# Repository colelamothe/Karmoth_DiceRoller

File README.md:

# Karmoth_DiceRoller
Compact battery powered polyhedral dice set

Currently available for purchase via: https://houseoftobes-shop.fourthwall.com/en-cad/products/karmoth-roller

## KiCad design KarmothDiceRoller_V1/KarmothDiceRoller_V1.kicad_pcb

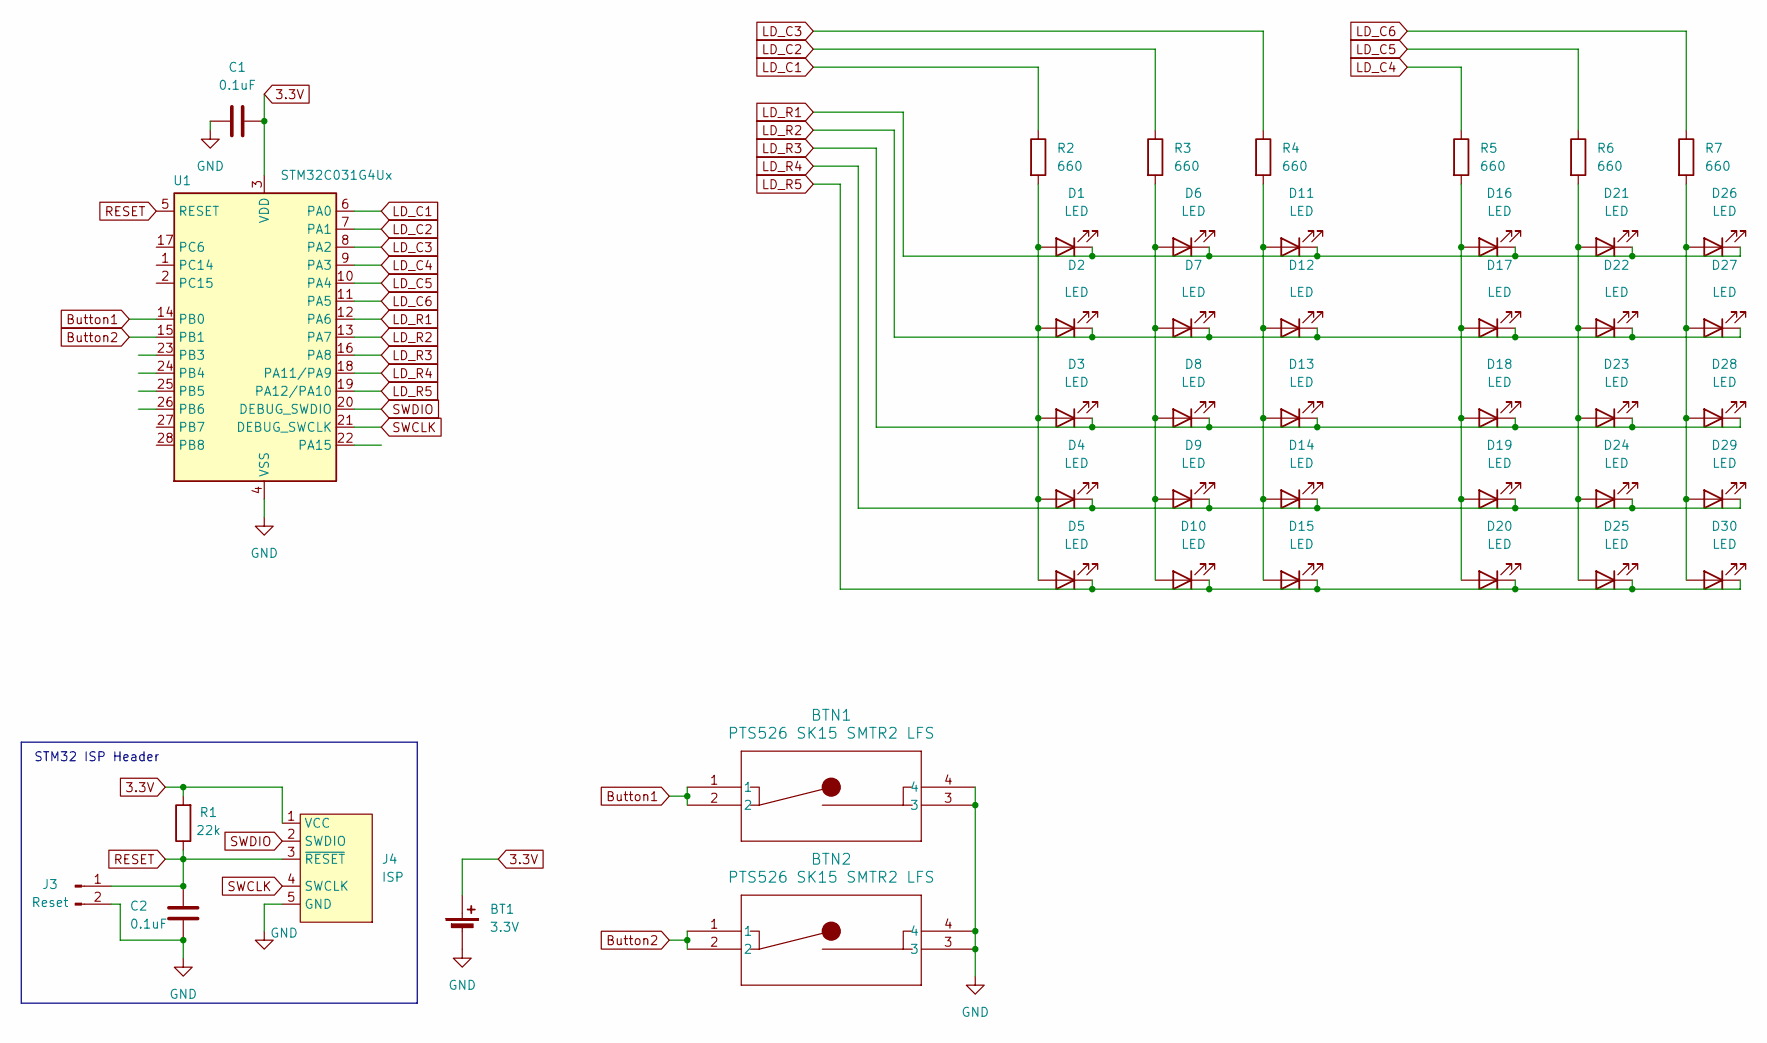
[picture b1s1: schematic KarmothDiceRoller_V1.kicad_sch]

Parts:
BT1: 3.3V; BatteryHolder_Keystone_3002_1x2032
BTN1, BTN2: PTS526 SK15 SMTR2 LFS; SMT_FS
C1, C2: 0.1uF; C_0805_2012Metric
D1, D2, D3, D4, D5, D6, D7, D8, D9, D10, D11, D12, D13, D14, D15, D16, D17, D18, D19, D20, D21, D22, D23, D24, D25, D26, D27, D28, D29, D30: LED; LED_0603_1608Metric
J3: Reset; PinHeader_1x02_P1.27mm_Vertical_SMD_Pin1Right
J4: ISP; PinHeader_1x05_P1.00mm_Vertical_SMD_Pin1Left
R1: 22k; R_0603_1608Metric
R2, R3, R4, R5, R6, R7: 660; R_0603_1608Metric
U1: STM32C031G4Ux; QFN-28_4x4mm_P0.5mm

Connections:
3.3V: BT1.1 (+), C1.1, J4.1 (VCC), R1.2, U1.3 (VDD)
Button1: BTN1.1, BTN1.2, U1.14 (PB0)
Button2: BTN2.1, BTN2.2, U1.15 (PB1)
GND: BT1.2 (-), BTN1.3, BTN1.4, BTN2.3, BTN2.4, C1.2, C2.2, J3.2, J4.5 (GND), U1.4 (VSS)
LD_C1: R2.1, U1.6 (PA0)
LD_C2: R3.1, U1.7 (PA1)
LD_C3: R4.1, U1.8 (PA2)
LD_C4: R5.1, U1.9 (PA3)
LD_C5: R6.1, U1.10 (PA4)
LD_C6: R7.1, U1.11 (PA5)
LD_R1: D1.1 (K), D6.1 (K), D11.1 (K), D16.1 (K), D21.1 (K), D26.1 (K), U1.12 (PA6)
LD_R2: D2.1 (K), D7.1 (K), D12.1 (K), D17.1 (K), D22.1 (K), D27.1 (K), U1.13 (PA7)
LD_R3: D3.1 (K), D8.1 (K), D13.1 (K), D18.1 (K), D23.1 (K), D28.1 (K), U1.16 (PA8)
LD_R4: D4.1 (K), D9.1 (K), D14.1 (K), D19.1 (K), D24.1 (K), D29.1 (K), U1.18 (PA11/PA9)
LD_R5: D5.1 (K), D10.1 (K), D15.1 (K), D20.1 (K), D25.1 (K), D30.1 (K), U1.19 (PA12/PA10)
unnamed: D1.2 (A), D2.2 (A), D3.2 (A), D4.2 (A), D5.2 (A), R2.2
unnamed: D6.2 (A), D7.2 (A), D8.2 (A), D9.2 (A), D10.2 (A), R3.2
unnamed: D11.2 (A), D12.2 (A), D13.2 (A), D14.2 (A), D15.2 (A), R4.2
unnamed: D16.2 (A), D17.2 (A), D18.2 (A), D19.2 (A), D20.2 (A), R5.2
unnamed: D21.2 (A), D22.2 (A), D23.2 (A), D24.2 (A), D25.2 (A), R6.2
unnamed: D26.2 (A), D27.2 (A), D28.2 (A), D29.2 (A), D30.2 (A), R7.2
RESET: C2.1, J3.1, J4.3 (~RESET), R1.1, U1.5 (RESET)
SWCLK: J4.4 (SWCLK), U1.21 (DEBUG_SWCLK)
SWDIO: J4.2 (SWDIO), U1.20 (DEBUG_SWDIO)

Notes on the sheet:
STM32 ISP Header

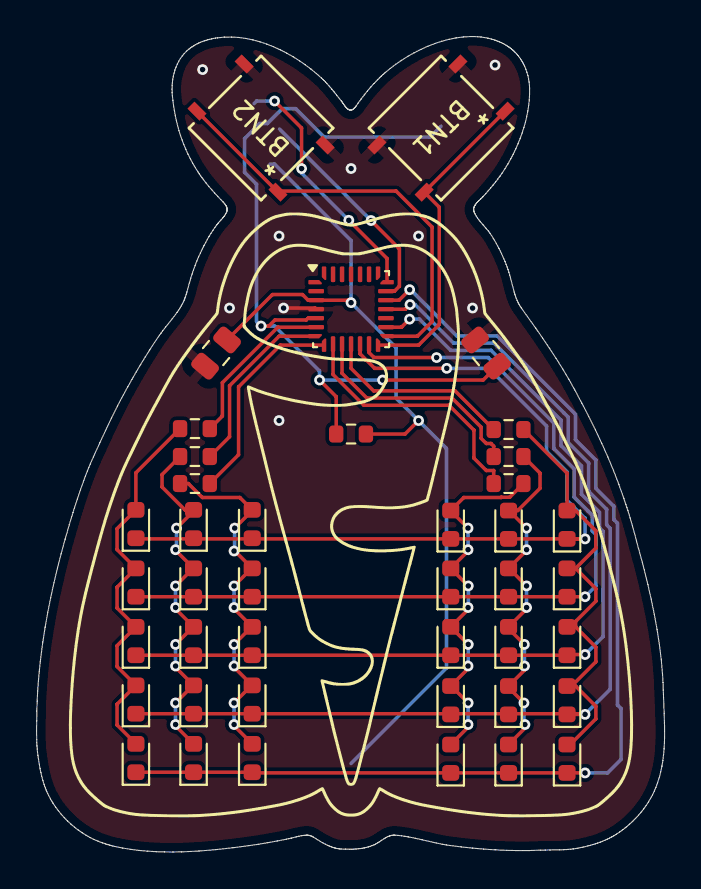
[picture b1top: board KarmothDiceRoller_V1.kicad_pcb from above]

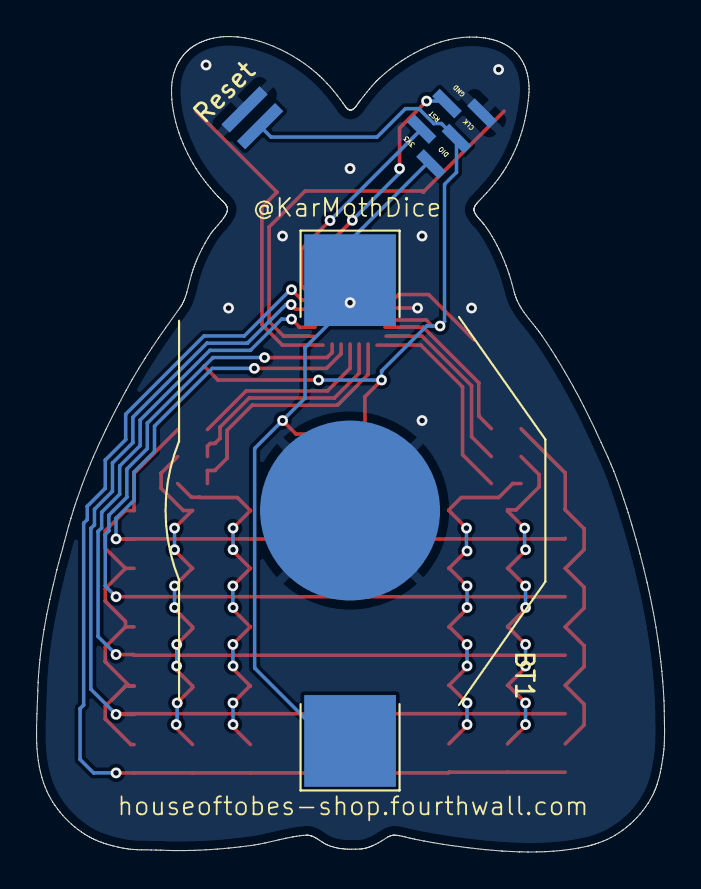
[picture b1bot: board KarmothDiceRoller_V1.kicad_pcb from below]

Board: 2 copper layers, 34.9 x 45.3 mm, 45 parts (3 on the bottom side), 24 nets.

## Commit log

2024-10-24 Initital Manufacturing Files
    3D printed case and PCB file initial upload
2024-10-24 Firmware Main source Files
    Extracted from CubeIDE file structure
2024-10-24 Complete firmware file structure for V1 roller
